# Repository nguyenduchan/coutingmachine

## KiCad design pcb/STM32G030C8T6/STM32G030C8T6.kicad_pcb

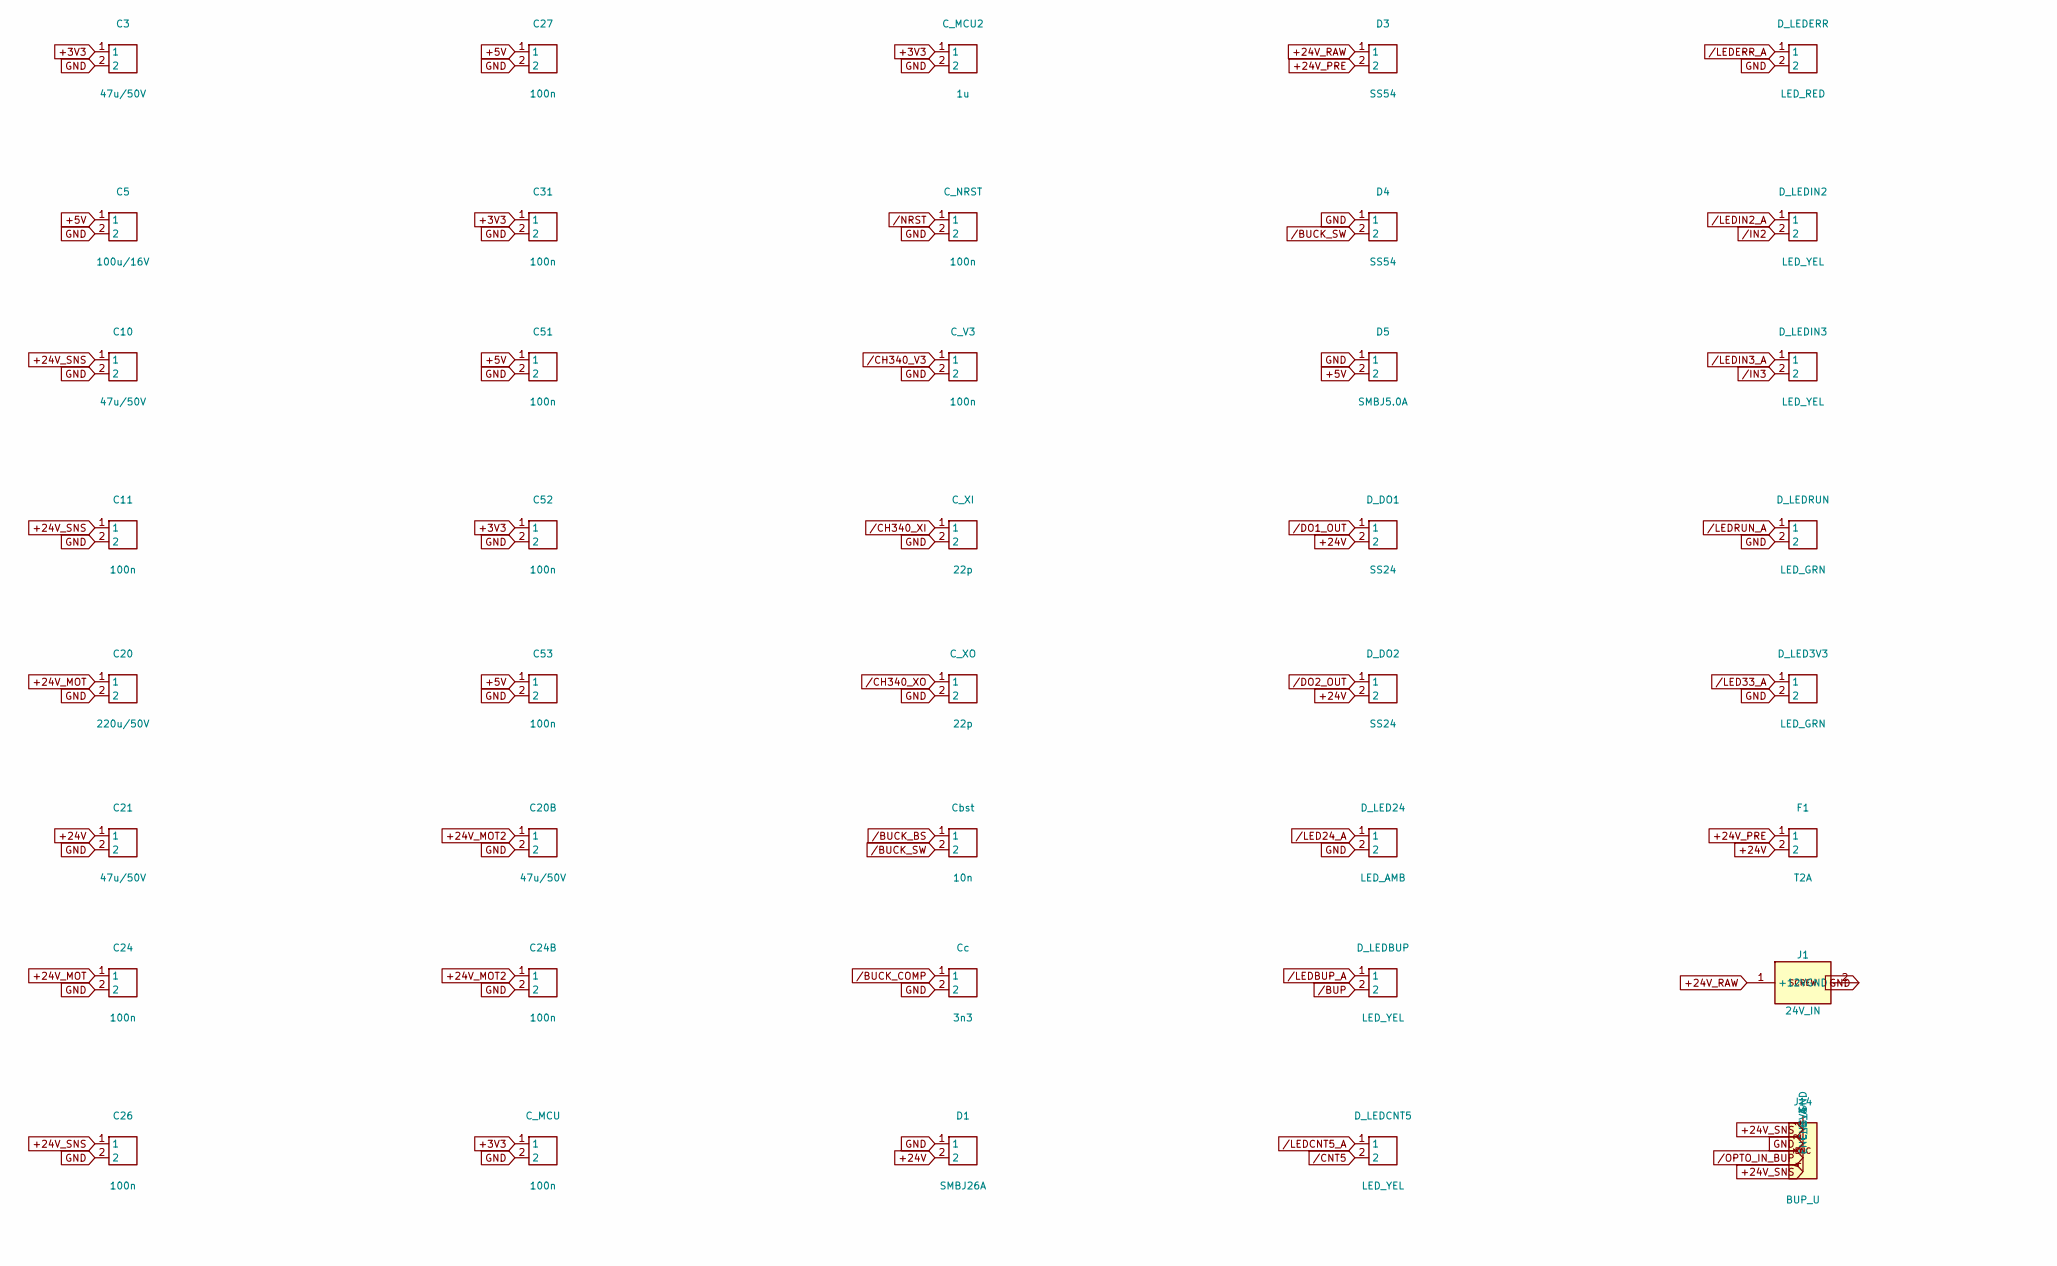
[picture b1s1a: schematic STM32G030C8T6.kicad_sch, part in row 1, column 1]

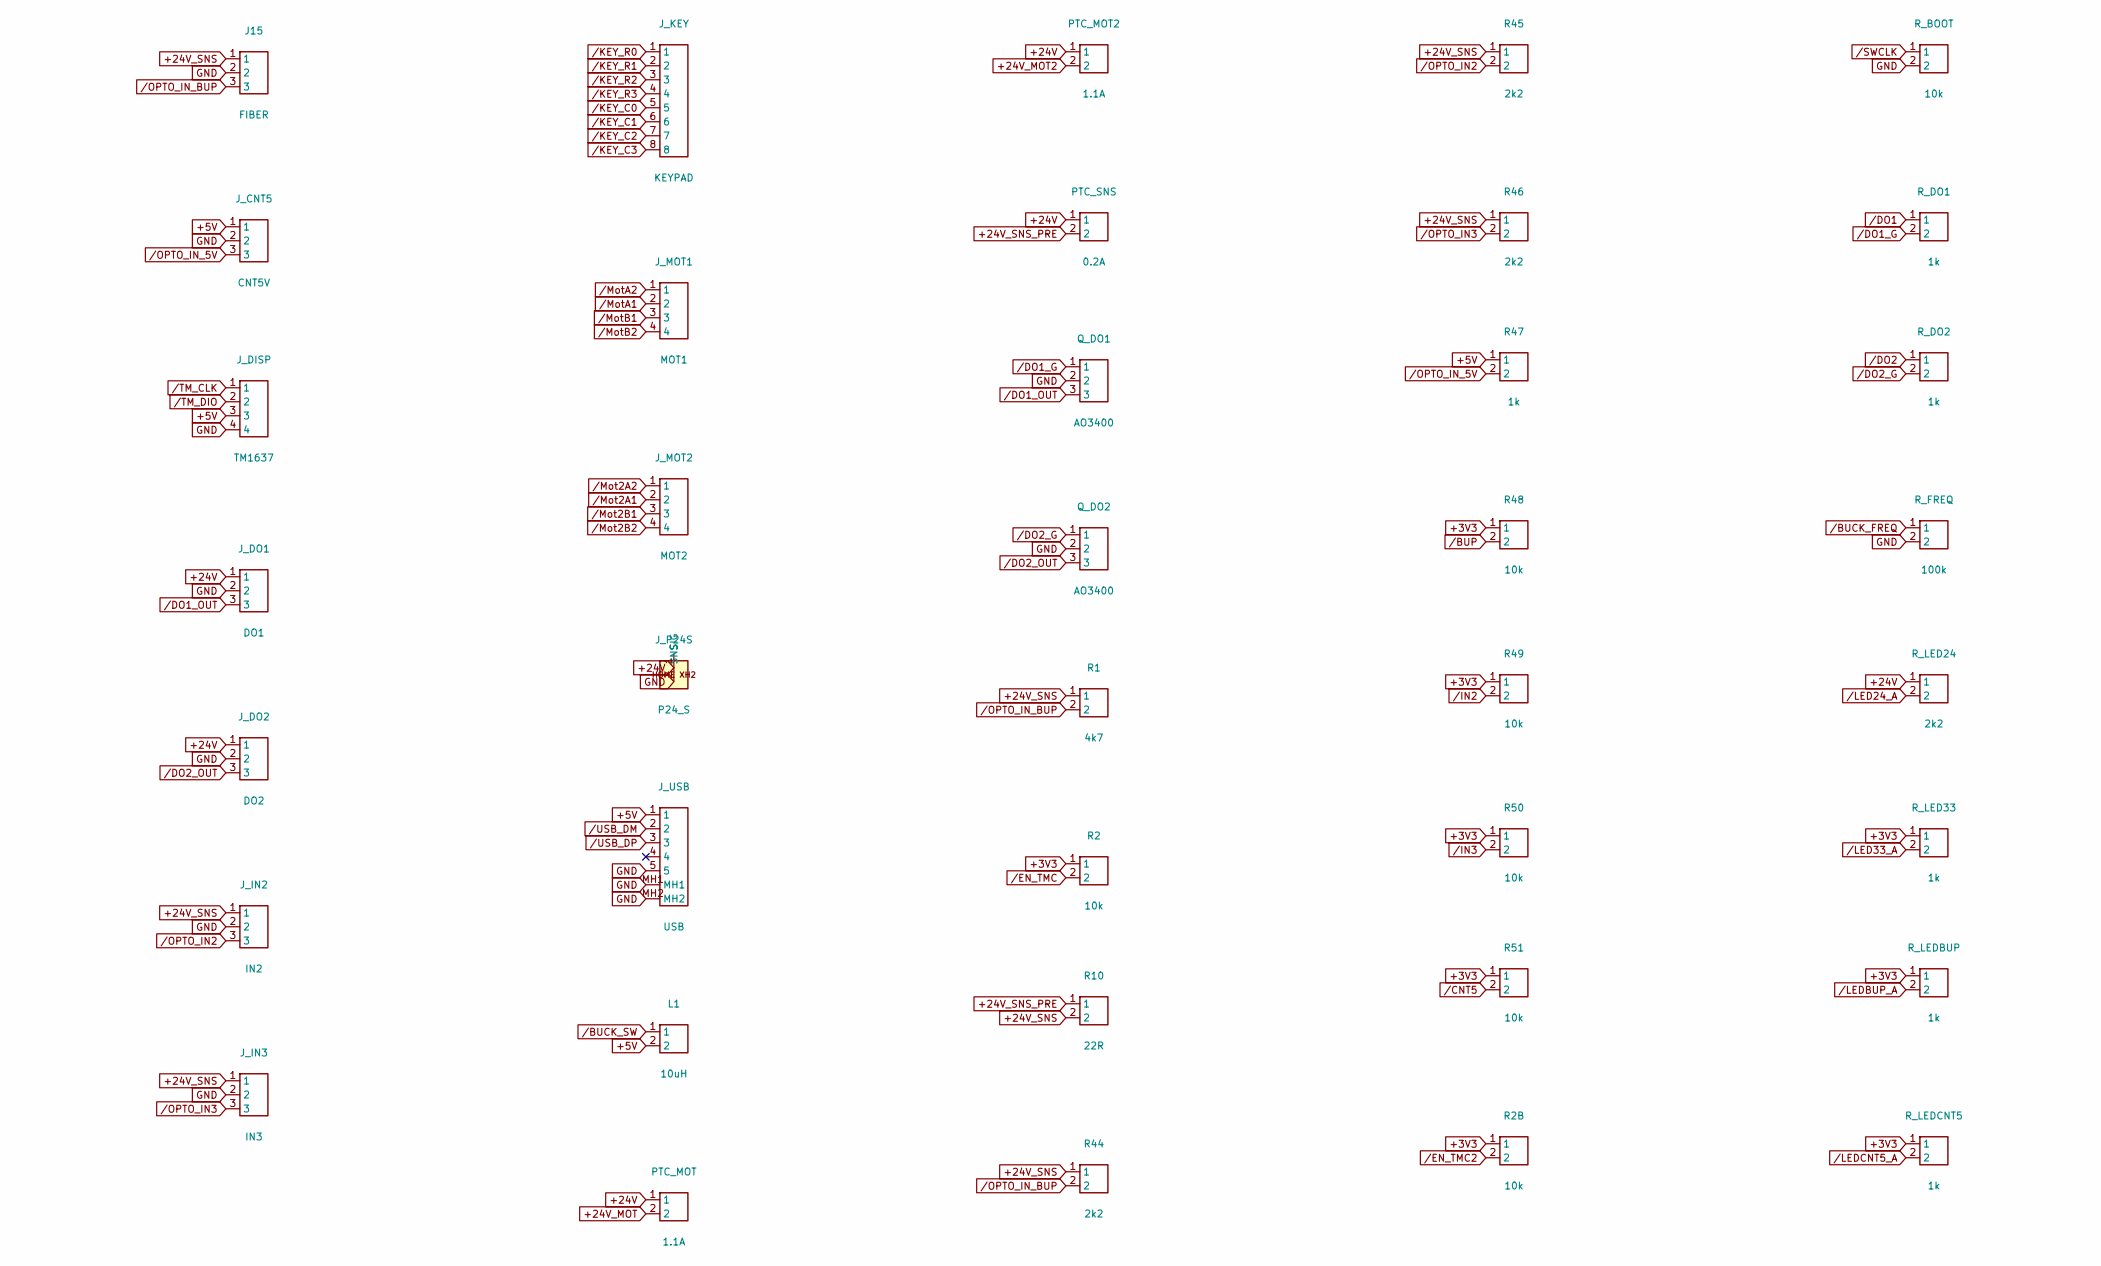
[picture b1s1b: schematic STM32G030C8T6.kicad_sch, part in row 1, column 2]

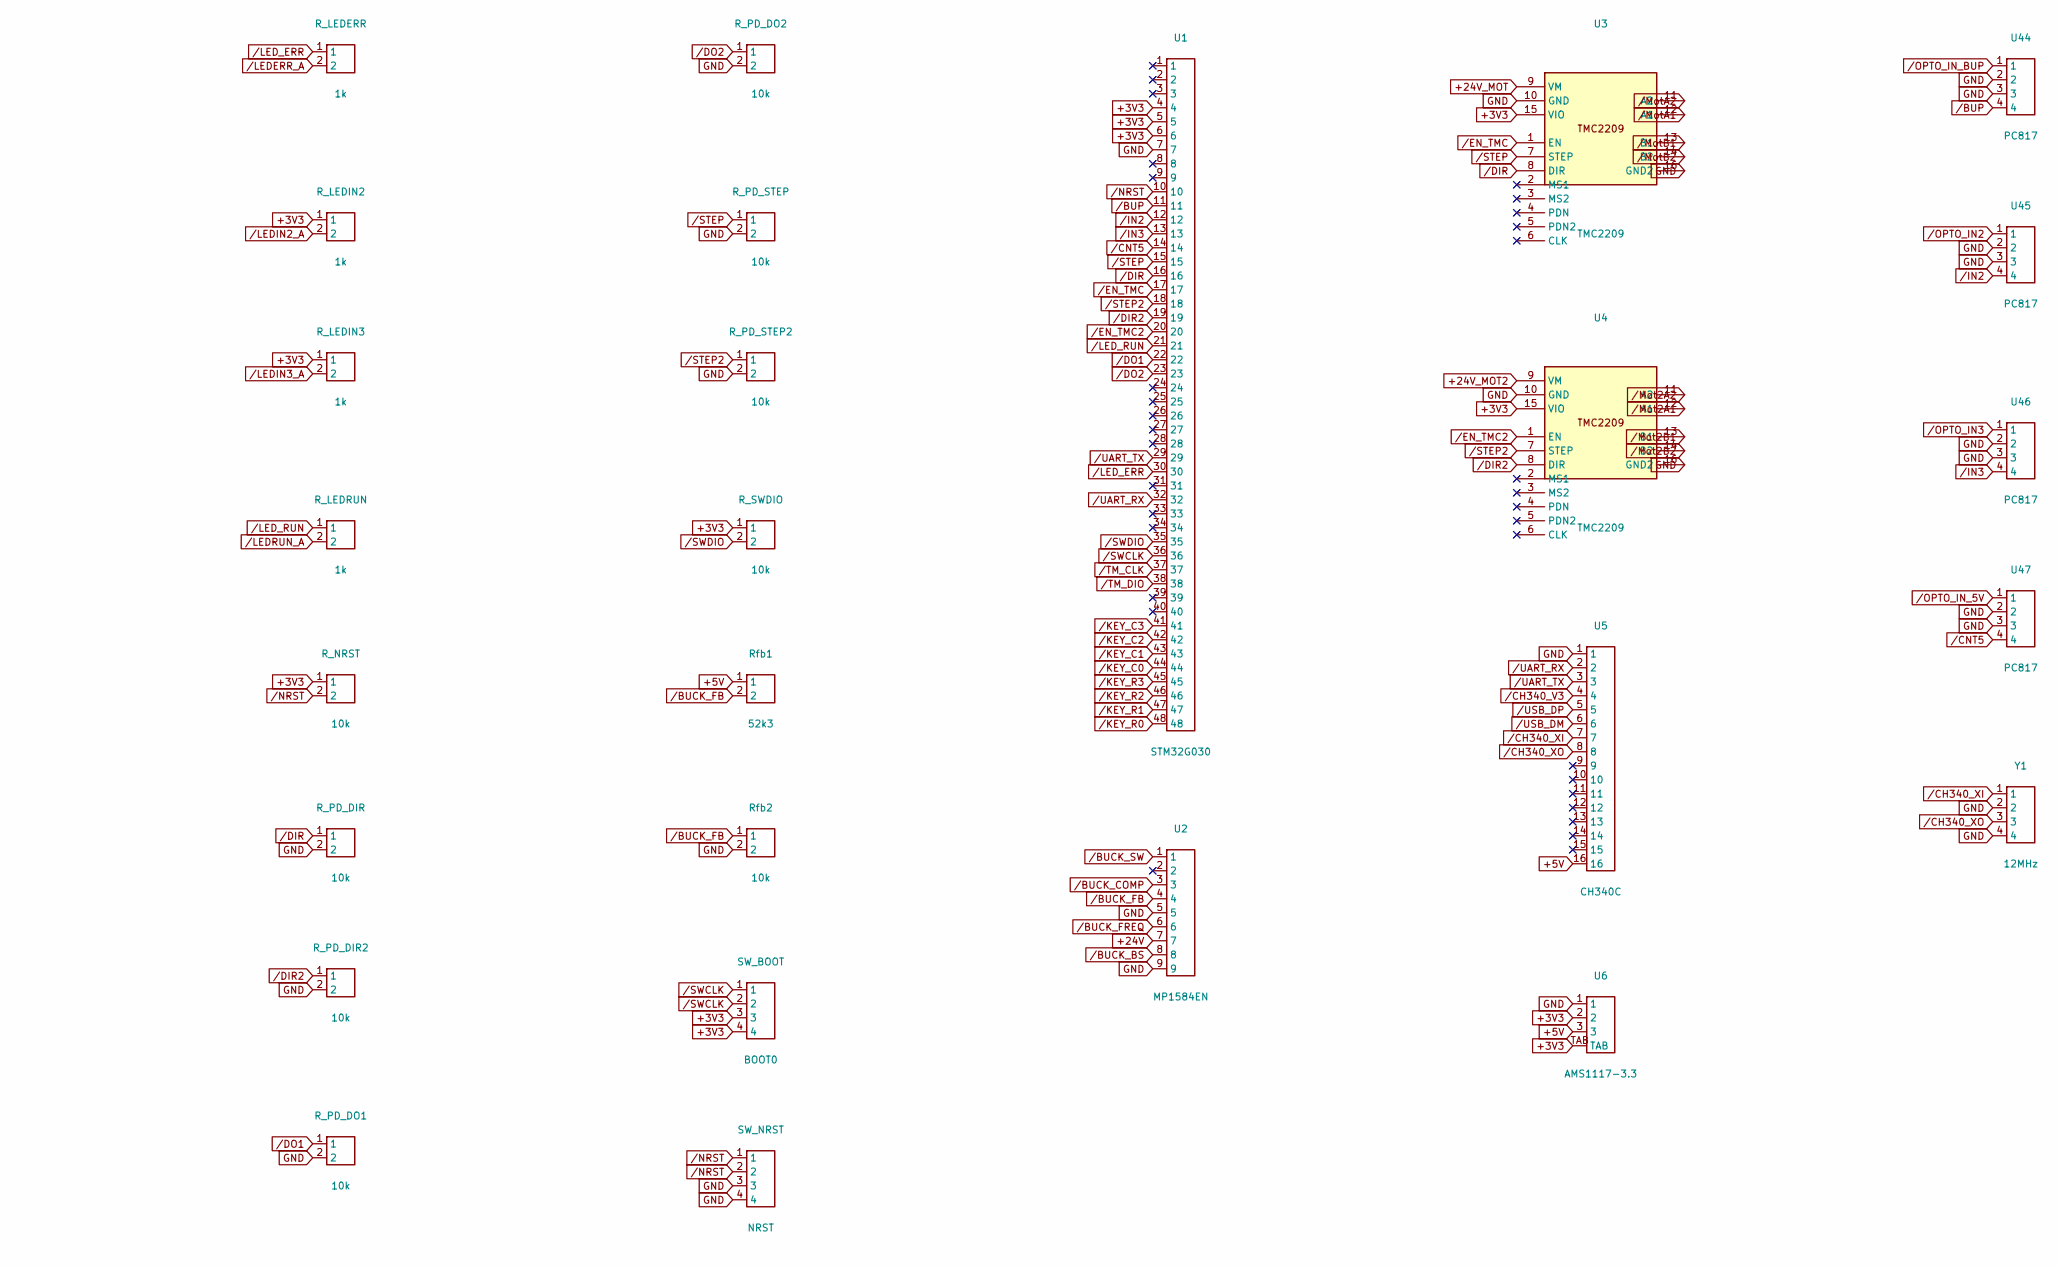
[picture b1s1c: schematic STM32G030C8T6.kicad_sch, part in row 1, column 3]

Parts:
C3, C10, C20B, C21: 47u/50V; CP_SMD_D6.3x8
C5: 100u/16V; CP_SMD_D6.3x5.8
C11, C24, C24B, C26, C27, C31, C51, C52, C53: 100n; C_0805_100n
C20: 220u/50V; CP_SMD_D8x10
C_MCU: 100n; C_0805_100n
C_MCU2: 1u; C_0805
C_NRST: 100n; C_0805_100n
C_V3: 100n; C_0805_100n
C_XI: 22p; C_0805
C_XO: 22p; C_0805
Cbst: 10n; C_0805
Cc: 3n3; C_0805
D1: SMBJ26A; Diode_SMB_TVS
D3, D4: SS54; Diode_SMA
D5: SMBJ5.0A; Diode_SMB_TVS
D_DO1, D_DO2: SS24; Diode_SMA
D_LED3V3: LED_GRN; LED_0805
D_LED24: LED_AMB; LED_0805
D_LEDBUP: LED_YEL; LED_0805
D_LEDCNT5: LED_YEL; LED_0805
D_LEDERR: LED_RED; LED_0805
D_LEDIN2, D_LEDIN3: LED_YEL; LED_0805
D_LEDRUN: LED_GRN; LED_0805
F1: T2A; Fuse_Holder_5x20_Open
J1: 24V_IN; TerminalBlock_2P_5.0mm
J14: BUP_U; JST_XH_04_Socket
J15: FIBER; JST_XH_03_Socket
J_CNT5: CNT5V; JST_XH_03_Socket
J_DISP: TM1637; Disp_XH_04_Socket
J_DO1: DO1; JST_XH_03_Socket
J_DO2: DO2; JST_XH_03_Socket
J_IN2: IN2; JST_XH_03_Socket
J_IN3: IN3; JST_XH_03_Socket
J_KEY: KEYPAD; PinHeader_1x08_Keypad
J_MOT1: MOT1; Mot_XH_04_Socket
J_MOT2: MOT2; Mot_XH_04_Socket
J_P24S: P24_S; JST_XH_02_Socket
J_USB: USB; USB_MicroB
L1: 10uH; L_SMD_6x6
PTC_MOT, PTC_MOT2: 1.1A; PTC_1812
PTC_SNS: 0.2A; PTC_1812
Q_DO1, Q_DO2: AO3400; MOSFET_SOT23
R1: 4k7; R_0805_4k7
R2, R2B, R48, R49, R50, R51: 10k; R_0805_10k
R10: 22R; R_1206_22R
R44, R45, R46: 2k2; R_0805_2k2
R47: 1k; R_0805_1k
R_BOOT: 10k; R_0805_10k
R_DO1, R_DO2: 1k; R_0805_1k
R_FREQ: 100k; R_0805_100k
R_LED24: 2k2; R_0805_2k2
R_LED33: 1k; R_0805_1k
R_LEDBUP: 1k; R_0805_1k
R_LEDCNT5: 1k; R_0805_1k
R_LEDERR: 1k; R_0805_1k
R_LEDIN2, R_LEDIN3: 1k; R_0805_1k
R_LEDRUN: 1k; R_0805_1k
R_NRST: 10k; R_0805_10k
R_PD_DIR, R_PD_DIR2: 10k; R_0805_10k
R_PD_DO1, R_PD_DO2: 10k; R_0805_10k
R_PD_STEP, R_PD_STEP2: 10k; R_0805_10k
R_SWDIO: 10k; R_0805_10k
Rfb1: 52k3; R_0805_4k7
Rfb2: 10k; R_0805_10k
SW_BOOT: BOOT0; SW_Push_6mm_SMD
SW_NRST: NRST; SW_Push_6mm_SMD
U1: STM32G030; STM32G030C8T6_LQFP48
U2: MP1584EN; MP1584EN_SOIC-8-EP
U3, U4: TMC2209; TMC2209_StepStick
U5: CH340C
U6: AMS1117-3.3; AMS1117_SOT223
U44, U45, U46, U47: PC817; PC817_SOP4
Y1: 12MHz; Crystal_SMD_3225

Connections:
+3V3: C3.1, C31.1, C52.1, C_MCU.1, C_MCU2.1, R2.1, R2B.1, R48.1, R49.1, R50.1, R51.1, R_LED33.1, R_LEDBUP.1, R_LEDCNT5.1, R_LEDIN2.1, R_LEDIN3.1, R_NRST.1, R_SWDIO.1, SW_BOOT.3, SW_BOOT.4, U1.4, U1.5, U1.6, U3.15 (VIO), U4.15 (VIO), U6.2, U6.TAB
+5V: C5.1, C27.1, C51.1, C53.1, D5.2, J_CNT5.1, J_DISP.3, J_USB.1, L1.2, R47.1, Rfb1.1, U5.16, U6.3
+24V: C21.1, D1.2, D_DO1.2, D_DO2.2, F1.2, J_DO1.1, J_DO2.1, J_P24S.1 (SIG), PTC_MOT.1, PTC_MOT2.1, PTC_SNS.1, R_LED24.1, U2.7
+24V_MOT: C20.1, C24.1, PTC_MOT.2, U3.9 (VM)
+24V_MOT2: C20B.1, C24B.1, PTC_MOT2.2, U4.9 (VM)
+24V_PRE: D3.2, F1.1
+24V_RAW: D3.1, J1.1 (+12V)
+24V_SNS: C10.1, C11.1, C26.1, J14.1 (GND), J14.4 (ENC_B), J15.1, J_IN2.1, J_IN3.1, R1.1, R10.2, R44.1, R45.1, R46.1
+24V_SNS_PRE: PTC_SNS.2, R10.1
/BUCK_BS: Cbst.1, U2.8
/BUCK_COMP: Cc.1, U2.3
/BUCK_FB: Rfb1.2, Rfb2.1, U2.4
/BUCK_FREQ: R_FREQ.1, U2.6
/BUCK_SW: Cbst.2, D4.2, L1.1, U2.1
/BUP: D_LEDBUP.2, R48.2, U1.11, U44.4
/CH340_V3: C_V3.1, U5.4
/CH340_XI: C_XI.1, U5.7, Y1.1
/CH340_XO: C_XO.1, U5.8, Y1.3
/CNT5: D_LEDCNT5.2, R51.2, U1.14, U47.4
/DIR: R_PD_DIR.1, U1.16, U3.8 (DIR)
/DIR2: R_PD_DIR2.1, U1.19, U4.8 (DIR)
/DO1: R_DO1.1, R_PD_DO1.1, U1.22
/DO1_G: Q_DO1.1, R_DO1.2
/DO1_OUT: D_DO1.1, J_DO1.3, Q_DO1.3
/DO2: R_DO2.1, R_PD_DO2.1, U1.23
/DO2_G: Q_DO2.1, R_DO2.2
/DO2_OUT: D_DO2.1, J_DO2.3, Q_DO2.3
/EN_TMC: R2.2, U1.17, U3.1 (EN)
/EN_TMC2: R2B.2, U1.20, U4.1 (EN)
/IN2: D_LEDIN2.2, R49.2, U1.12, U45.4
/IN3: D_LEDIN3.2, R50.2, U1.13, U46.4
/KEY_C0: J_KEY.5, U1.44
/KEY_C1: J_KEY.6, U1.43
/KEY_C2: J_KEY.7, U1.42
/KEY_C3: J_KEY.8, U1.41
/KEY_R0: J_KEY.1, U1.48
/KEY_R1: J_KEY.2, U1.47
/KEY_R2: J_KEY.3, U1.46
/KEY_R3: J_KEY.4, U1.45
/LED24_A: D_LED24.1, R_LED24.2
/LED33_A: D_LED3V3.1, R_LED33.2
/LEDBUP_A: D_LEDBUP.1, R_LEDBUP.2
/LEDCNT5_A: D_LEDCNT5.1, R_LEDCNT5.2
/LEDERR_A: D_LEDERR.1, R_LEDERR.2
/LEDIN2_A: D_LEDIN2.1, R_LEDIN2.2
/LEDIN3_A: D_LEDIN3.1, R_LEDIN3.2
/LEDRUN_A: D_LEDRUN.1, R_LEDRUN.2
/LED_ERR: R_LEDERR.1, U1.30
/LED_RUN: R_LEDRUN.1, U1.21
/Mot2A1: J_MOT2.2, U4.12 (A1)
/Mot2A2: J_MOT2.1, U4.11 (A2)
/Mot2B1: J_MOT2.3, U4.13 (B1)
/Mot2B2: J_MOT2.4, U4.14 (B2)
/MotA1: J_MOT1.2, U3.12 (A1)
/MotA2: J_MOT1.1, U3.11 (A2)
/MotB1: J_MOT1.3, U3.13 (B1)
/MotB2: J_MOT1.4, U3.14 (B2)
/NRST: C_NRST.1, R_NRST.2, SW_NRST.1, SW_NRST.2, U1.10
/OPTO_IN2: J_IN2.3, R45.2, U45.1
/OPTO_IN3: J_IN3.3, R46.2, U46.1
/OPTO_IN_5V: J_CNT5.3, R47.2, U47.1
/OPTO_IN_BUP: J14.3 (ENC_A), J15.3, R1.2, R44.2, U44.1
/STEP: R_PD_STEP.1, U1.15, U3.7 (STEP)
/STEP2: R_PD_STEP2.1, U1.18, U4.7 (STEP)
/SWCLK: R_BOOT.1, SW_BOOT.1, SW_BOOT.2, U1.36
/SWDIO: R_SWDIO.2, U1.35
/TM_CLK: J_DISP.1, U1.37
/TM_DIO: J_DISP.2, U1.38
/UART_RX: U1.32, U5.2
/UART_TX: U1.29, U5.3
/USB_DM: J_USB.2, U5.6
/USB_DP: J_USB.3, U5.5
GND: C3.2, C5.2, C10.2, C11.2, C20.2, C20B.2, C21.2, C24.2, C24B.2, C26.2, C27.2, C31.2, C51.2, C52.2, C53.2, C_MCU.2, C_MCU2.2, C_NRST.2, C_V3.2, C_XI.2, C_XO.2, Cc.2, D1.1, D4.1, D5.1, D_LED3V3.2, D_LED24.2, D_LEDERR.2, D_LEDRUN.2, J1.2 (GND), J14.2 (3V3), J15.2, J_CNT5.2, J_DISP.4, J_DO1.2, J_DO2.2, J_IN2.2, J_IN3.2, J_P24S.2 (SNS), J_USB.5, J_USB.MH1, J_USB.MH2, Q_DO1.2, Q_DO2.2, R_BOOT.2, R_FREQ.2, R_PD_DIR.2, R_PD_DIR2.2, R_PD_DO1.2, R_PD_DO2.2, R_PD_STEP.2, R_PD_STEP2.2, Rfb2.2, SW_NRST.3, SW_NRST.4, U1.7, U2.5, U2.9, U3.10 (GND), U3.16 (GND2), U4.10 (GND), U4.16 (GND2), U5.1, U6.1, U44.2, U44.3, U45.2, U45.3, U46.2, U46.3, U47.2, U47.3, Y1.2, Y1.4

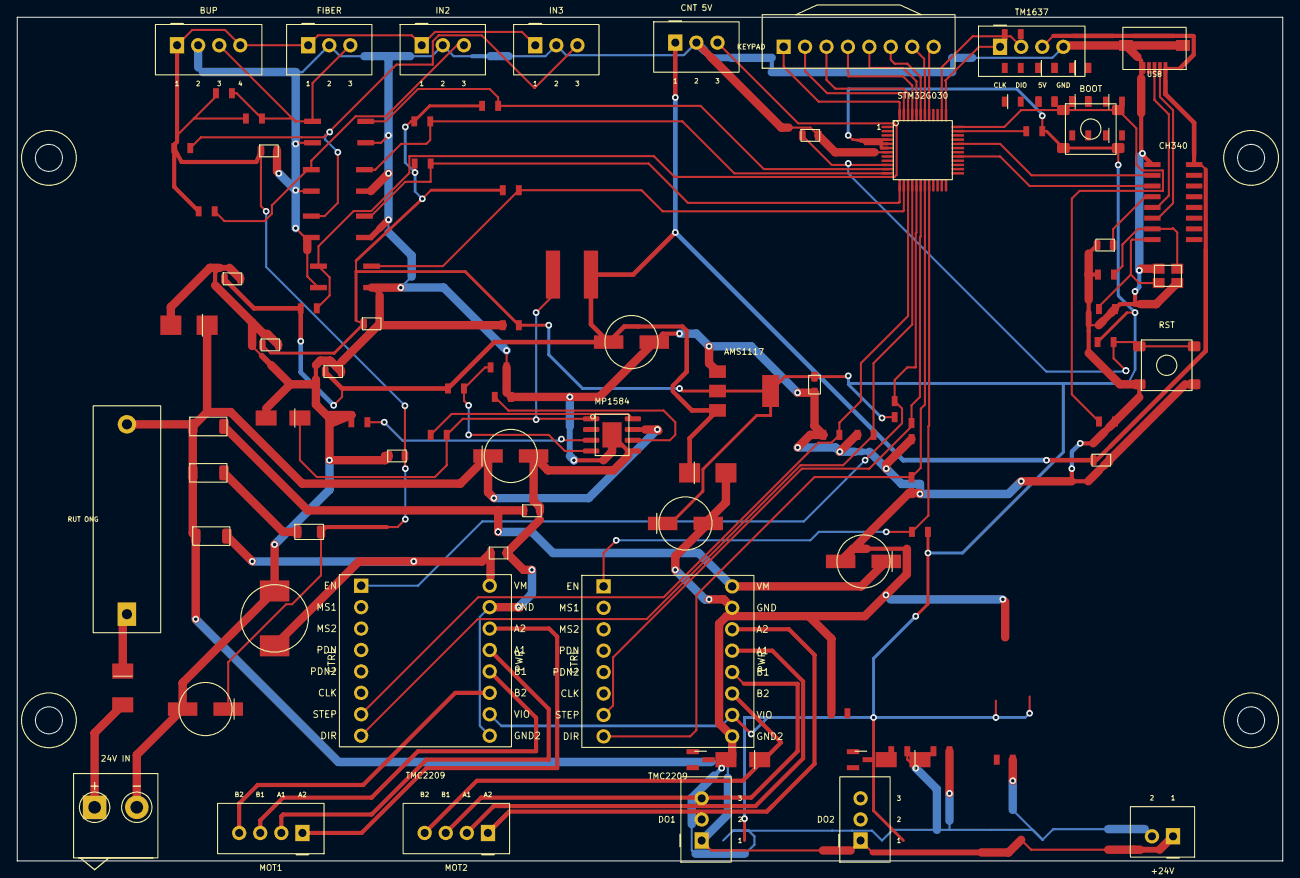
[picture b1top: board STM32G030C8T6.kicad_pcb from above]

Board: 2 copper layers, 150.0 x 100.0 mm, 109 parts (0 on the bottom side), 73 nets.

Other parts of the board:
H1, H2, H3, H4: M3; MountingHole_M3

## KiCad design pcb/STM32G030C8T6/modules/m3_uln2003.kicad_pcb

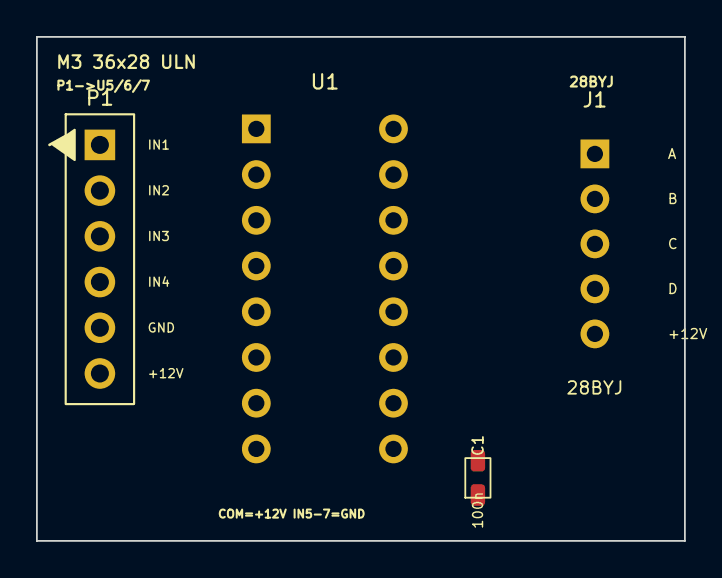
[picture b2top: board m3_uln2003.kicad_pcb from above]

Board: 2 copper layers, 36.0 x 28.0 mm, 4 parts (0 on the bottom side), 10 nets, no tracks yet.

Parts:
C1: 100n; C_0805_100n
J1: 28BYJ; JST_XH_05_BYJ
P1: 1x6_to_U5-7; PinHeader_1x06_Module
U1: ULN2003AN

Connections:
+12V: C1.1, J1.5, P1.6, U1.9
GND: C1.2, P1.5, U1.5, U1.6, U1.7, U1.8
IN1: P1.1, U1.1
IN2: P1.2, U1.2
IN3: P1.3, U1.3
IN4: P1.4, U1.4
OUT1: J1.1, U1.16
OUT2: J1.2, U1.15
OUT3: J1.3, U1.14
OUT4: J1.4, U1.13

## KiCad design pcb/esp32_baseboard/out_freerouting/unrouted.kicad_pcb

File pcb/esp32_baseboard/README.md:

# ESP32-S3 Baseboard — BOM (ULN2003 + 74HC595-24IO module)

**BOM đầy đủ (audit PCB):** [`BOM.md`](BOM.md) · **Module / mua hàng:** [`MODULES.md`](MODULES.md) · **Review:** [`PCB_REVIEW.md`](PCB_REVIEW.md).

PSU **Mean Well 12V**. Limits = mechanical HOME only (J8/J10/J12). Board = jacks + drivers; **D3/F1/D1 + PC817×4 hàn trên carrier**; **M3 gần động cơ**.

## On-board (carrier)

| Ref | Part | Role |
|-----|------|------|
| J1 | Terminal 2P 5.0 | 12V PSU in (RAW) |
| **D3** | **SS54** Schottky | Series chống ngược |
| **F1** | Đế 5×20 + ống **T3.15A** | Cầu chì rút ống |
| **D1** | **P6KE15A** TVS | Clamp surge trên +12V |
| **U41–U44** | **PC817** DIP-4 ×4 | HOME1-3 + BUP opto |
| **R41–R44 / R45–R48** | 2k2 / 10k | LED series / collector PU |
| **C26** | 100n | SNS HF @ opto |
| U1 | ESP32-S3-DevKitC-1 N16R8 | MCU |
| U2 | MP1584EN 5V | Logic buck (only) |
| U3 | TMC2209 | NEMA17 trên Mot (không J2) |
| J24 / J25 | Header cái 1×6 + 1×24 | Cắm **74HC595-24IO** (U10 mua rời) |
| R4 | 10k axial | LDEN/`OE` pull-up → +3V3 |
| U5–U7 | Socket **1×6** → **M3** | Cáp gần 28BYJ; JST trên M3 |
| R1 | 4k7 | BUP NPN pull-up → OPTO_IN4 |
| R2/R3 | 10k | EN_TMC PU / BLOWER PD |
| R10 / C10 / C11 | 10Ω / 47µ / 100n | Star SNS |
| D2 | **SS24** flyback | Blower inductive kick (rail TVS = D1) |
| C20 | 470µ | Bulk @ TMC |
| C21 | 220µ | Shared ULN VCC bulk |
| C24 / C25 | 100n 0805 | HF @ TMC / ULN |
| ~~J2~~ | — | **XOÁ** (Mot trên U3) |
| ~~J5–J7~~ | — | **XOÁ** (28BYJ trên M3) |
| ~~J30 / M1~~ | — | **XOÁ** — D3/F1/D1 trên carrier |
| J8/J10/J12 | **JST-XH 2P** | HOME dry NC SIG/SNS |
| J14 | **JST-XH 4P** | BUP-30S |
| J15 | **JST-XH 3P** | Buzzer 5V |
| J16 | **JST-XH 4P** | AOD4184 blower |
| J18 | **JST-XH 4P** | EC11 ENC |
| J17/J23 | 1×09 / 1×05 @2.54 | TFT LCD + touch |

**Pluggable (JLCPCB snap):** [`modules/`](modules/) — `m3_uln2003`, `submodules_panel`. Chi tiết SL: [`BOM.md`](BOM.md).

**Deleted:** J2, J5–J7, J30/M1, J31A/B/M2; PC817 trên carrier.

> All footprints on **TOP (F.Cu)**; **đi dây ưu tiên B.Cu** + **GND pour F+B**.

## An toàn điện — nguy cơ chập / cháy / cắm ngược

Chuỗi nguồn: `J1 → D3 SS54 → F1 đế 5×20 T3.15A → D1 TVS → +12V`.  
Opto: `PC817×4 + 2k2/10k` trên carrier. Panel: `modules/submodules_panel.kicad_pcb` (M3).

### Nguy cơ điện

| Mức | Nguy cơ | Bảo vệ | Ghi chú |
|-----|---------|--------|---------|
| **Cao** | Cắm **ngược** dây 12 V tại J1 | **D3 Schottky series** + silk `+`/`−`/`NO REVERSE` | Screw **không** khóa cơ — bắt buộc D3 + dây đỏ/đen |
| **Cao** | 28BYJ **5 V** trên rail 12 V | Chỉ mua **28BYJ-12V** | R-8 MODULES |
| **Cao** | NEMA17 stall / Vref cao | C20; F1 ống; FW timeout | Heatsink TMC |
| Trung | Chập +12V sau F1 | **F1 5×20 T3.15A** (rút ống) + track Power 1,0 mm | Dự phòng ống |
| Trung | Surge / ESD 12 V | **D1 P6KE15A** | K = +12V |
| Trung | Bơm inductive kick | **D2 SS24** @ J16 | Rail TVS = D1 |
| Trung | 595 boot → ULN kéo tải | **R4 OE pull-up** | Bắt buộc |
| Trung | J16 MOSFET cắm lệch | Silk pin + **JST-XH 4P keyed** | PWM/GND/+12V/FAN− |
| Thấp | HOME SNS chập GND | R2k2 + opto trên M2 | Không nối GPIO←12V |
| Thấp | Chập +5V logic | MP1584 limit nội | Tuỳ chọn PTC 0,5 A |

### Giắc / đế — ưu tiên chống ngược

| Giắc | Loại hiện tại | Chống ngược? | Hành động lắp |
|------|---------------|--------------|---------------|
| **J1** | Screw 2P 5,0 | Silk + D3 điện | Dây **đỏ=+ / đen=−**; không đảo |
| **F1** | Đế 5×20 PCB | — | Rút ống khi chảy |
| J8/10/12 | **JST-XH 2P** | **Có** | Dry NC SIG/SNS |
| J14 | **JST-XH 4P** | **Có** | BUP Brn/Blu/Blk/Wht — pin4 CTRL→+V (Light ON) |
| J15/J16/J18 | **XH-3 / XH-4** | **Có** | Không hàn pin trần |
| J17+J23 | TFT 9+5 @2.54 | Module 2 hàng cố định | Không đảo hàng |
| J24/J25 | 595 CTRL+Q | Module Shopee cố định | Khớp silkscreen module |
| U1/U3/U5–7 | Socket module | Pin1 notch / silkscreen | Đúng hướng module |

**Không thay:** D3 ≥5 A Schottky; F1 ống **T ~3 A** 5×20; D1 uni TVS ~15 V; **không** bỏ khóa JST-XH field I/O.

## GPIO

| Function | GPIO |
|----------|------|
| HOME OUT1-3 / BUP OUT4 | IO1,2,4,5 |
| SER / SRCLK / RCLK / OE_595 | IO10–13 |
| TMC STEP/DIR/EN | IO16–18 |
| TFT SPI + BL + touch | IO39/40/42/21/46/45 + MISO47 T_CS48 T_IRQ6 |
| ENC_A / ENC_B | IO38 / IO41 |
| Buzzer / blower | IO9 / IO3 |
| Spare | IO7,8,14,15 |

## Chống nhiễu khi đi dây (EMI / EMC)

Board 2 lớp, tải động cơ + SPI TFT + opto 12 V — nhiễu chủ yếu từ **return path**, **loop diện tích**, và **đường dài dưới module**. Áp dụng khi route / review:

| # | Đề xuất | Trên board này |
|---|---------|----------------|
| N1 | **Pour GND hai mặt** (F.Cu + B.Cu), thermal relief pad THT | Zone GND inset 0,5 mm mép; fill sau FreeRouting |
| N2 | **Tín hiệu dài trên B.Cu**; F.Cu chỉ fan-out pad→via (A0) | FreeRouting prefer B ngang / F dọc |
| N3 | **Return GND sát tín hiệu** — tránh “đảo” GND đứt bởi bus dài | Pour liên tục; via stitch khi đổi lớp |
| N4 | **Nguồn rộng + star tại J1** — +12V / GND không dùng chung đường mỏng với GPIO | Netclass Power **1,00 mm**; star silk tại J1 |
| N5 | **Bulk sát tải nhiễu** — C20 ≤10 mm TMC VM; C21 chung ULN COM | Placement floorplan |
| N6 | **Vòng motor nhỏ** — MotA/B cặp gần nhau; 28BYJ trên **M3 gần motor** | E10.5 |
| N7 | **Tách êm / ồn** — HMI+MCU đông; POWER+TMC+ULN+opto tây/nam | Eco cụm E11 |
| N8 | **SPI / ENC ngắn** — J17/J23/J18 gần U1; không vòng quanh motor | Floorplan HMI |
| N9 | **Cách ly field 12 V** — HOME/BUP vào opto; không nối thẳng GPIO | PC817 + R series |
| N10 | **Via một cỡ 0,4/0,8** (A8); ưu tiên đổi lớp tại pad THT (A1) | Ít via “lạ”, dễ fab |
| N11 | **Không chạy bus dưới cụm module trên F.Cu** | A0 + Manual tick |
| N12 | Clearance track↔lỗ ≥ A7 (0,45 mm trong DSN) | `route_freerouting` inject |

**Khi fab / lắp:** dây motor xoắn hoặc cặp gần nhau; GND PSU ngắn tới J1; cable TFT/ENC tránh song song dài với dây 12 V motor.

Chi tiết bắt buộc: `PCB_REVIEW.md` mục **A0 / A8 / A10 / E10**.

## Regenerate

```powershell
$env:PCB_SKIP_MAZE=1; python gen_power_carrier.py
python gen_schematic_from_pcb.py
& "$env:LOCALAPPDATA\Programs\KiCad.0in\python.exe" route_freerouting.py
python verify_all.py
```

Board **180×145 mm** (bội 5; layout XY đóng băng; Eco ≥10 mm mép). Modules ≥10 mm mép; ≥10 mm MCU Eco; ≥8 mm giữa Ecos. Power netclass **1,00 mm** (peak +12V ~2,3 A).

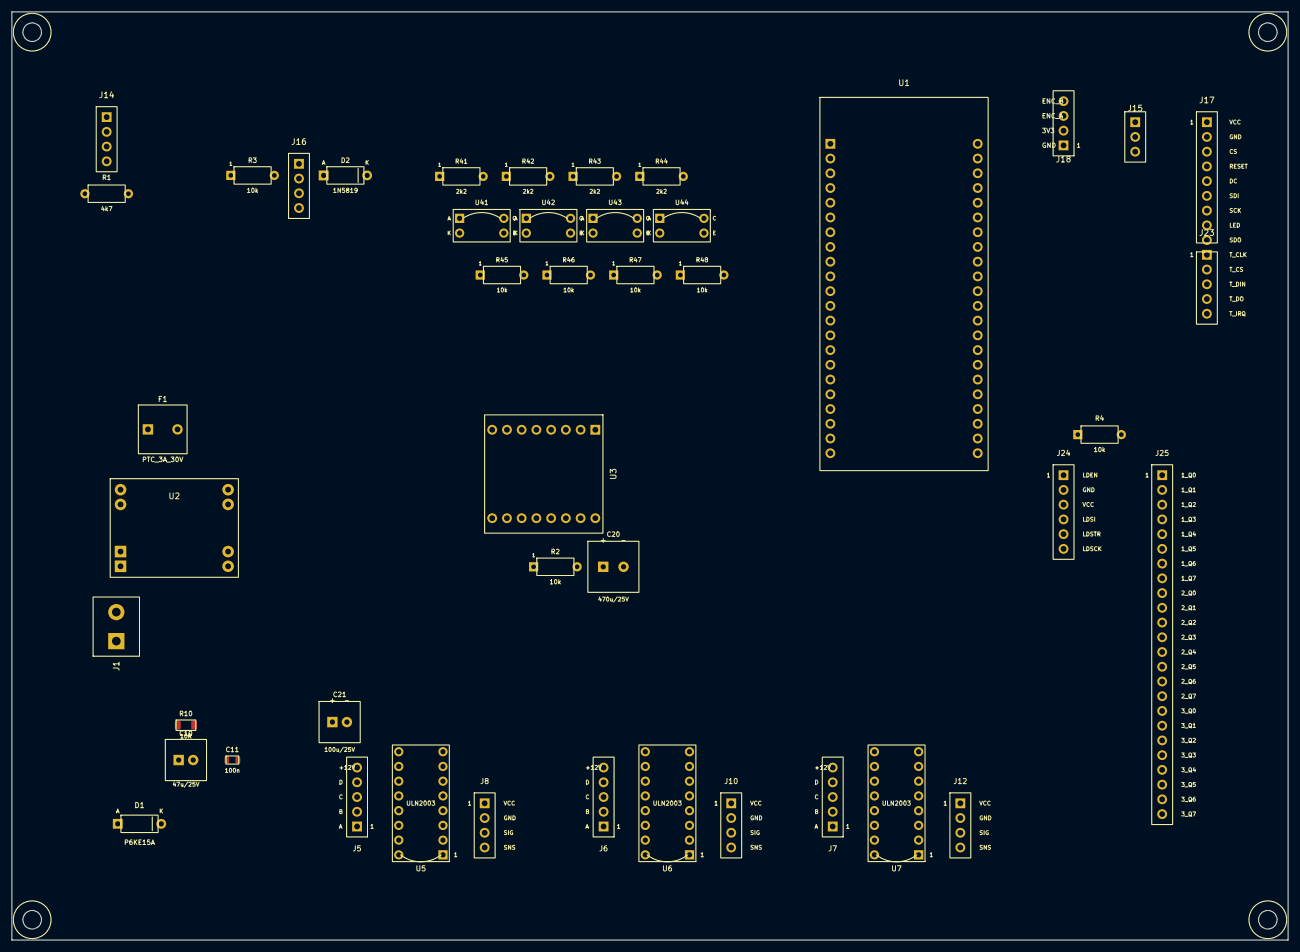
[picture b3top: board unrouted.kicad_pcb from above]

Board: 2 copper layers, 220.0 x 160.0 mm, 49 parts (0 on the bottom side), 63 nets, no tracks yet.

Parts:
C10: 47u/25V; CP_Radial_D6_47u_25V
C11: 100n; C_0805_100n
C20: 470u/25V; CP_Radial_D8_470u_25V
C21: 100u/25V; CP_Radial_D6_100u_25V
D1: P6KE15A; Diode_TVS_DO41
D2: 1N5819; Diode_TVS_DO41
F1: PTC_3A_30V; Fuse_PTC_Radial_5.1mm
H1, H2, H3, H4: M3; MountingHole_M3
J1: Screw_12V_IN; TerminalBlock_2P_5.0mm
J5, J6, J7: 28BYJ48; PinHeader_1x05_BYJ
J8: END_HOME1; PinHeader_1x04_Endstop
J10: END_HOME2; PinHeader_1x04_Endstop
J12: END_HOME3; PinHeader_1x04_Endstop
J14: BUP_30S; PinHeader_1x04_BUP30S
J15: BUZZER_5V; PinHeader_1x03_Buzzer
J16: AOD4184; PinHeader_1x04_MOSFET
J17: TFT_LCD; PinHeader_1x09_TFT_LCD
J18: EC11_ENC; PinHeader_1x04_ENC
J23: TFT_TP; PinHeader_1x05_TFT_TP
J24: 595_CTRL; PinHeader_1x06_595CTRL
J25: 595_Q; PinHeader_1x24_595Q
R1: 4k7; R_Axial_4k7_BUP
R2, R3, R4, R45, R46, R47, R48: 10k; R_Axial_4k7_BUP
R10: 10R; R_1206_10R
R41, R42, R43, R44: 2k2; R_Axial_4k7_BUP
U1: ESP32_S3_DevKitC_1; ESP32_S3_DevKitC_44Pin_Socket
U2: MP1584_5V3A
U3: TMC2209; TMC2209_StepStick
U5, U6, U7: ULN2003AN
U41, U42, U43, U44: PC817; PC817_DIP4

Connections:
+3V3: J17.1, J18.2, J24.3, R2.2, R4.2, R45.1, R46.1, R47.1, R48.1, U1.1, U1.2, U3.15
+5V: J15.1, U1.21, U2.4
+12V: C20.1, C21.1, D1.2, D2.1, F1.2, J5.5, J6.5, J7.5, J16.3, R10.1, U2.1, U3.9, U5.9, U6.9, U7.9
+12V_RAW: F1.1, J1.1
+12V_SNS: C10.1, C11.1, J8.4, J10.4, J12.4, J14.1, R1.1, R10.2
BLOWER: J16.1, R3.1, U1.13
BLW_RET: D2.2, J16.4
BUZZER: J15.3, U1.15
BYJ1_A: J5.1, U5.16
BYJ1_B: J5.2, U5.15
BYJ1_C: J5.3, U5.14
BYJ1_D: J5.4, U5.13
BYJ2_A: J6.1, U6.16
BYJ2_B: J6.2, U6.15
BYJ2_C: J6.3, U6.14
BYJ2_D: J6.4, U6.13
BYJ3_A: J7.1, U7.16
BYJ3_B: J7.2, U7.15
BYJ3_C: J7.3, U7.14
BYJ3_D: J7.4, U7.13
DIR: U1.10, U3.8
ENC_A: J18.3, U1.32
ENC_B: J18.4, U1.29
EN_TMC: R2.1, U1.11, U3.1
GND: C10.2, C11.2, C20.2, C21.2, D1.1, J1.2, J14.2, J15.2, J16.2, J17.2, J18.1, J24.2, R3.2, U1.22, U1.23, U1.43, U1.44, U2.2, U2.3, U3.10, U3.16, U5.8, U6.8, U7.8, U41.2, U41.3, U42.2, U42.3, U43.2, U43.3, U44.2, U44.3
OE_595: J24.1, R4.1, U1.19
OPTO_A1: R41.2, U41.1
OPTO_A2: R42.2, U42.1
OPTO_A3: R43.2, U43.1
OPTO_A4: R44.2, U44.1
OPTO_IN1: J8.3, R41.1
OPTO_IN2: J10.3, R42.1
OPTO_IN3: J12.3, R43.1
OPTO_IN4: J14.3, R1.2, R44.1
OPTO_OUT1: R45.2, U1.26, U41.4
OPTO_OUT2: R46.2, U1.27, U42.4
OPTO_OUT3: R47.2, U1.4, U43.4
OPTO_OUT4: R48.2, U1.5, U44.4
RCLK: J24.5, U1.18
SER: J24.4, U1.16
SRCLK: J24.6, U1.17
SR_Q0: J25.1, U5.1
SR_Q1: J25.2, U5.2
SR_Q2: J25.3, U5.3
SR_Q3: J25.4, U5.4
SR_Q4: J25.5, U6.1
SR_Q5: J25.6, U6.2
SR_Q6: J25.7, U6.3
SR_Q7: J25.8, U6.4
SR_Q8: J25.9, U7.1
SR_Q9: J25.10, U7.2
SR_Q10: J25.11, U7.3
SR_Q11: J25.12, U7.4
STEP: U1.9, U3.7
TFT_BL: J17.8, U1.37
TFT_CS: J17.3, U1.28
TFT_DC: J17.5, U1.40
TFT_MISO: J23.4, U1.39
TFT_MOSI: J17.6, J23.3, U1.30
TFT_RST: J17.4, U1.14
TFT_SCK: J17.7, J23.1, U1.31
T_CS: J23.2, U1.38
T_IRQ: J23.5, U1.6
